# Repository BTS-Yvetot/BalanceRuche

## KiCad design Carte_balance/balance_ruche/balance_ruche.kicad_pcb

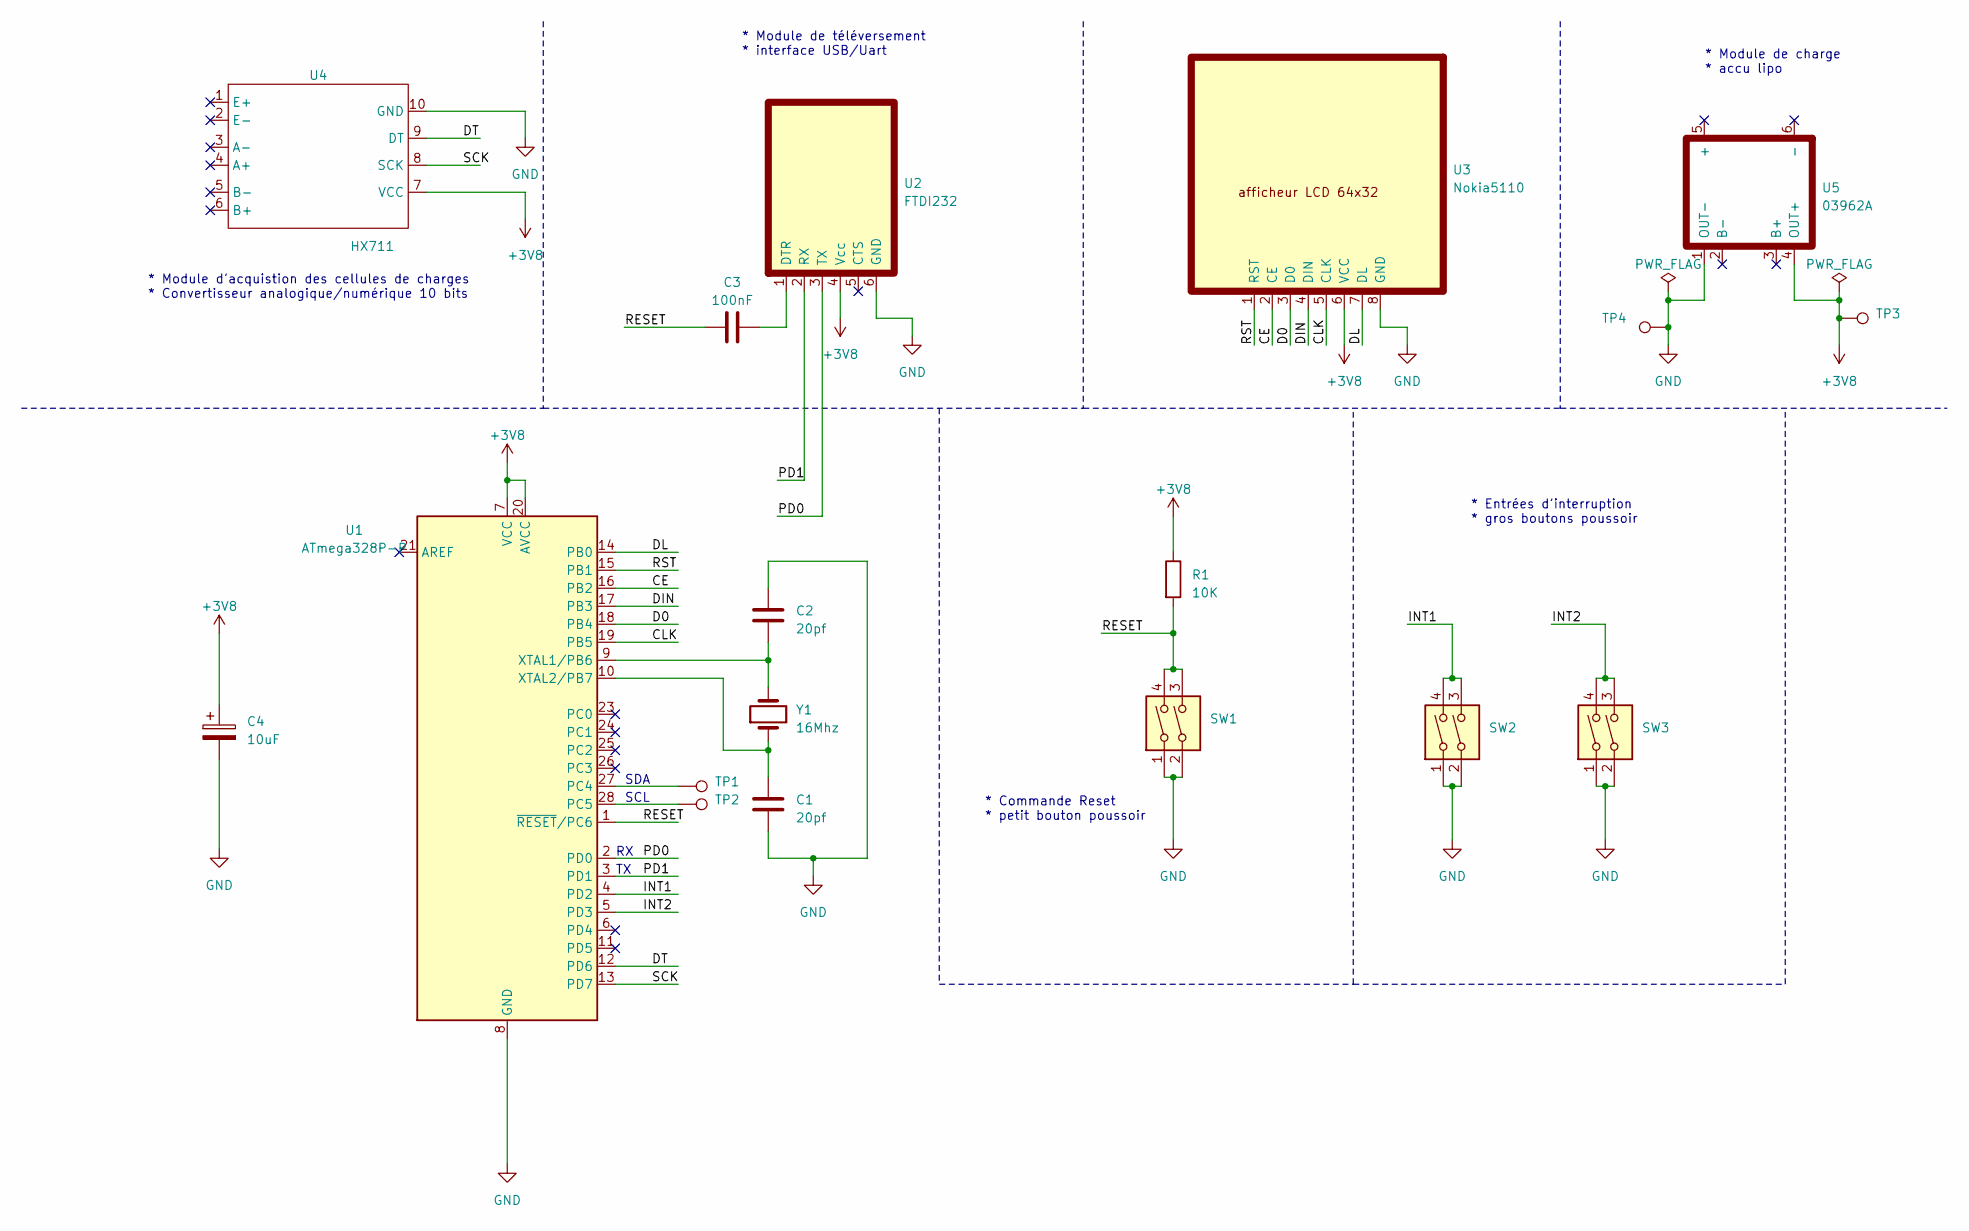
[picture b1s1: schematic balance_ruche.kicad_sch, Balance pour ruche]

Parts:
C1, C2: 20pf; C_Disc_D8.0mm_W5.0mm_P7.50mm
C3: 100nF; C_Rect_L7.2mm_W2.5mm_P5.00mm_FKS2_FKP2_MKS2_MKP2
C4: 10uF; CP_Radial_D5.0mm_P2.50mm
R1: 10K; R_Axial_DIN0309_L9.0mm_D3.2mm_P12.70mm_Horizontal
SW1: SW_DIP_x02; micro_switch
SW2, SW3: SW_DIP_x02; bouton_poussoir
TP1, TP2, TP3, TP4: TestPoint; TestPoint_THTPad_2.0x2.0mm_Drill1.0mm
U1: ATmega328P-P; DIP_28_Atmel328P
U2: FTDI232; FTDI232RL
U3: Nokia5110; Nokia5510
U4: HX711
U5: 03962A; Charger_accu
Y1: 16Mhz; Crystal_HC49-4H_Vertical

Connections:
+3V8: C4.1, R1.1, TP3.1, U1.7 (VCC), U1.20 (AVCC), U2.4 (Vcc), U3.6 (VCC), U4.7 (VCC), U5.4 (OUT+)
/CE: U1.16 (PB2), U3.2 (CE)
/CLK: U1.19 (PB5), U3.5 (CLK)
/D0: U1.18 (PB4), U3.3 (D0)
/DIN: U1.17 (PB3), U3.4 (DIN)
/DL: U1.14 (PB0), U3.7 (DL)
/DT: U1.12 (PD6), U4.9 (DT)
/INT1: SW2.3, SW2.4, U1.4 (PD2)
/INT2: SW3.3, SW3.4, U1.5 (PD3)
/PD0: U1.2 (PD0), U2.3 (TX)
/PD1: U1.3 (PD1), U2.2 (RX)
/RESET: C3.1, R1.2, SW1.3, SW1.4, U1.1 (~RESET/PC6)
/RST: U1.15 (PB1), U3.1 (RST)
/SCK: U1.13 (PD7), U4.8 (SCK)
GND: C1.2, C2.1, C4.2, SW1.1, SW1.2, SW2.1, SW2.2, SW3.1, SW3.2, TP4.1, U1.8 (GND), U1.22 (GND), U2.6 (GND), U3.8 (GND), U4.10 (GND), U5.1 (OUT-)
unnamed: TP1.1, U1.27 (PC4)
unnamed: TP2.1, U1.28 (PC5)
unnamed: C2.2, U1.9 (XTAL1/PB6), Y1.2
unnamed: C1.1, U1.10 (XTAL2/PB7), Y1.1
unnamed: C3.2, U2.1 (DTR)

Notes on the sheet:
* Commande Reset * petit bouton poussoir
* Module de charge * accu lipo
SDA
SCL
* Entrées d'interruption * gros boutons poussoir
* Module de téléversement * interface USB/Uart
* Module d'acquistion des cellules de charges * Convertisseur analogique/numérique 10 bits

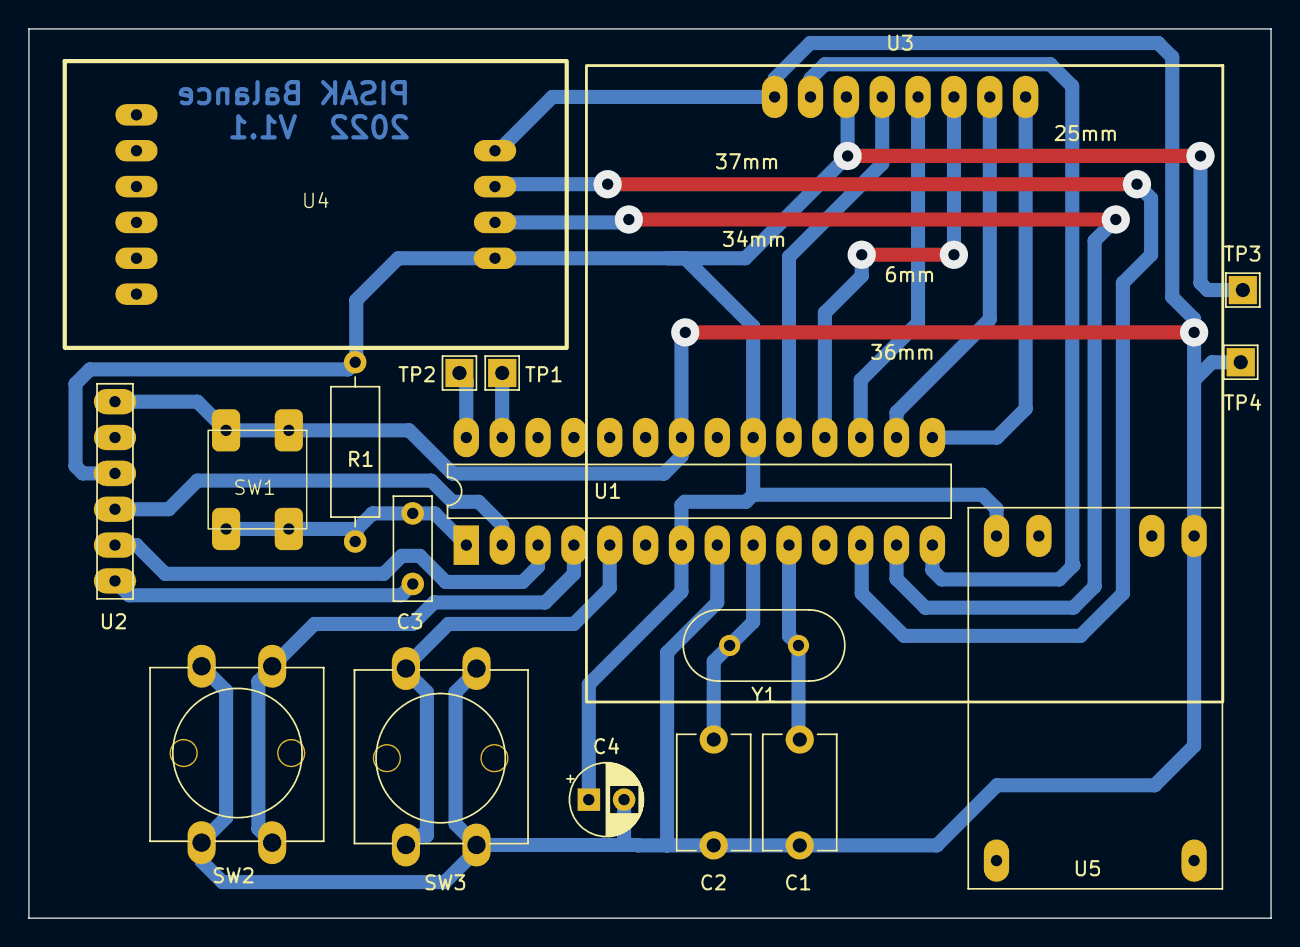
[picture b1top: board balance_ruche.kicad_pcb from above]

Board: 2 copper layers, 88.0 x 63.0 mm, 18 parts (0 on the bottom side), 20 nets.

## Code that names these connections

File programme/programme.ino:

#include <SPI.h>
#include <avr/wdt.h>
#include <avr/sleep.h>
#include "HX711.h"
#include "fonction.h"

#define RST 9  //broche PB1 patte 15 sur l'atmel reset de l'afficheur SPI
#define CE  10 //broche PB2 patte 16 sur l'atmel chip enable de l'afficheur SPI
#define DO  12 //broche PB4 patte 18 sur l'atmel miso de l'afficheur SPI
#define DL  8  //broche PB0 patte 14 sur l'atmel retro eclairage de l'afficheur
#define CLK 13 //broche PB5 patte 19 sur l'atmel
#define DIN 11 //broche PB3 patte 17 sur l'atmel

#define DT  6  //ligne data du convertisseur pour cellule de charge HX711 (broche PD6 patte 12 sur l'atmel)
#define SCK 7  //ligne d'horloge pour le convertisseur HX711 (broche PD7 patte 13 sur l'atmel)

#define debug false

//afficheur NOKIA 5510

#include <Adafruit_GFX.h>
#include <Adafruit_PCD8544.h>

//Branchement des deux signaux Dout et Clock sur PD6 et PD7
const int LOADCELL_DOUT_PIN = DT;    
const int LOADCELL_SCK_PIN = SCK;       


//on garde les broches 4 et 5 de l'atmel (PD2 et PD3) comme entree d'interuption pour les futurs boutons poussoirs
//d'ou le deplacement du reset de l'afficheur LCD

//instanciation du capteur et de l'afficheur
//afficheur nokia 5110 utilisé en SPI hardware donc broche 11 et 13
//nécessairement utilisées (patte 17 pour mosi et 19 pour clock sur l'atmel 328p)
Adafruit_PCD8544 lcd = Adafruit_PCD8544(CLK, DIN, DO, CE, RST);     //afficheur Nokia sur liaison SPI hardware
                                                      

//variable pour les routines d'interruption

volatile bool routineWDT = false;
volatile bool routineINT0 = false;
volatile bool routineINT1 = false;
volatile float poids=0.0;
volatile unsigned long chrono;
volatile unsigned int compteur=0;

//traitement des trois interruptions possible (watchdog,INT0 sur PD2 et INT1 sur PD3)
ISR(WDT_vect) {
  routineWDT = true;
  compteur++;
}

ISR(INT0_vect) {                             //mise en mémoire du poids sur PD2
  EIMSK = 0x00;                              //desactivation des inter externes
  WDTCSR = (1 << WDCE) | (1 << WDE);         //desactivation du chien de garde
  WDTCSR = 0b0000000;                        //
  routineINT0 = true;
}

ISR(INT1_vect) {                             //rétro-eclairage sur PD3
  EIMSK = 0x00;                              //desactivation des inter externes
  WDTCSR = (1 << WDCE) | (1 << WDE);         //desactivation du chien de garde
  WDTCSR = 0b0000000;                        //
  chrono=millis();
  routineINT1 = true;
}  


int main (void){
  init();                             //initialisation pour utiliser l'environnement arduino
  HX711 balance;                      //instanciation d'un objet HX711
  boolean start=true;                 //variable pour le premier lancement du programme
  float memPoids=0.0; 

#if debug
  Serial.begin(9600);
#endif

//broche retro eclairage et interuption
  pinMode(DL, OUTPUT);         //retro_eclairage actif a l'etat haut
  pinMode(2, INPUT_PULLUP);   //interupteur sur broche D2 INT0 : mise en memoire
  pinMode(3, INPUT_PULLUP);   //interupteur sur broche D3 INT1 : retro-eclairage
 
//initialisation de la balance  
  balance.begin(LOADCELL_DOUT_PIN, LOADCELL_SCK_PIN,128);   //gain de 128 sur le channel A du convertisseur (le 32 reservé pour le canal B)

//(tare + facteur de convertion)
  while (!balance.is_ready());                              //attention !! fonction bloquante tant que Dout n'est pas au niveau bas
  balance.set_scale(2297.f);                                //valeur trouvee après la procedure de calibration
  balance.tare(10);                                         //permet de soustraire la valeur au démarrage pour afficher 0 (tarage de la balance) avec 10 mesures

// Afficheur lcd
  lcd.begin();
  lcd.setRotation(0);         //(pose problème pour l'affichage de plusieur info sans clearDisplay !! laisser 0 par défaut)
  lcd.clearDisplay();
  lcd.setContrast(60);        //!!!! a régler pour chaque afficheur....
  lcd.display();

#if debug
  Serial.println("balance prête !!");
#endif

  //affichage de la page de présentation
  lcd.clearDisplay();
  lcd.cp437(true);                    // Utilisation des 256 caractères de la police Cp437
  lcd.drawRect(0, 0, 83, 47, BLACK);  // cadre de l'ecran
  lcd.setTextSize(1);                 // taille normale 1:1 pixel soit 5x7 pixels
  lcd.setTextColor(BLACK);            // couleur unique
  lcd.setCursor(2,2);                 // affichage de la trame de la page
  lcd.print("mem :");
  lcd.setCursor(65,2);
  lcd.print("kg");
  lcd.setCursor(60,29);
  lcd.print(F(" Kg"));
  lcd.display();


  
  while(1){
//toute les 8 secondes ou la premiere fois 
    if(routineWDT || start){              //réveil par le chien de garde watchdog         

      start=false;                        //pour afficher les valeurs uniquement au premier lancement sans attendre 8 seconde
      poids=(balance.get_units(10)/10);
      if (poids<=0.0){                    // permet de gérer le poids si négatif
        poids=0.0;
      }
//mesure du poids
#if debug
      Serial.println(F("le watchdog à déclenché !"));
      Serial.print(poids,1);           //affiche la valeur en Kg avec 1 chiffre derrière la virgule (on tient compte ici du 
      Serial.println(" kg");                                //facteur de convertion (contrairement a get_value()
#endif

//gestion du retro eclairage      
      if (compteur>=1){
         digitalWrite(DL,LOW);             //gestion du rétro-éclairage
         compteur=0;
      }     
//effacement des anciennes données
      effacePoids(lcd);

//affichage des données
      //poids LCD
      lcd.setTextSize(2);              // taille normale 1:1 pixel soit 5x7 pixels
      lcd.setTextColor(BLACK, WHITE);  // couleur unique
      lcd.setCursor(4, 29);
      if (poids>=100.00){
        lcd.print(poids,1);
      }
      else {
        lcd.print(poids);
      }
      lcd.display();
      balance.power_down();                                 //place le capteur en basse consommation
      routineWDT=false;           
    }
    //si appuye sur le bouton de droite 
    if (routineINT0) {
      wdt_reset();
      digitalWrite(DL,HIGH);                       //allumage du rétro-éclairage
      balance.power_down(); 
      routineINT0 = false;
      wdt_reset();
#if debug
      Serial.println("INT0 a declenche !!");
      Serial.println("fin de la routine INT0");
#endif
    }
    //si appuye sur le bouton de gauche
    if (routineINT1) {
      memPoids=poids;
      effaceMem(lcd);
      lcd.setTextSize(1);              // taille normale 1:1 pixel soit 5x7 pixels
      lcd.setCursor(35, 2);
      if(memPoids>=100.00){
        lcd.print(memPoids,1);
      }
      else{
        lcd.print(memPoids);
      }
      lcd.display();
      while((!digitalRead(3))&&((millis()-chrono)<3000));
      if(!digitalRead(3)){               //appuie sur le bouton de gauche pendant 3 secondes
        effacePoids(lcd);
        balance.tare(10);
        poids=(balance.get_units(10)/10);
        lcd.setTextSize(2);              // taille normale 1:1 pixel soit 5x7 pixels
        lcd.setTextColor(BLACK, WHITE);  // couleur unique
        lcd.setCursor(4, 29);
        if (poids<=0.0){
          poids=0.0;
        }
        lcd.print(poids);
        lcd.display();
        while(!digitalRead(3));         //tant que l'on a pas relaché le bouton
        wdt_reset();
      }
#if debug
      Serial.println("INT1 a declenche !!");
      Serial.println("fin de la routine INT1");
#endif
      balance.power_down();
      routineINT1 = false;            //interuption prise en compte
    }

    //autorise les interruptions des deux boutons poussoirs
    EIFR = 0b00000011; //efface les drapeaux avant de valider les interruptions à nouveau!!
    EIMSK = 0x03;     //validation des interruptions sur les pattes PD2 et PD3 (INT0 et INT1)
    EICRA = 0b00001010; //front descendant sur INT0 et INT1 (compatible avec le mode sleep utilisé)

    //autorise les interruptions du watchdog (toutes les 8 secondes )
    wdt_reset();
    WDTCSR = (1 << WDCE) | (1 << WDE);          // Déverrouille les bits de configuration du Watchdog (procédure spécifiée par le fabricant)
    WDTCSR = 0b01100001;                        // Mise à 1 des bits WDP3 et WDIE, pour activer les interruption toutes les 8 secondes
                  
    // mise en sommeil
    set_sleep_mode(SLEEP_MODE_PWR_DOWN);
    sleep_enable();
    // Et on met le µC en sommeil maintenant
#if debug
    Serial.println("Mise en sommeil du µC");
    Serial.println("");
    Serial.flush();         // On attend la fin de la transmission des données séries, avant de mettre le microcontrôleur en sommeil
#endif
    sleep_mode();
#if debug
    Serial.println("réveil!!");
#endif
    balance.power_up();                                   //active le capteur (sortie du mode basse consommation)
  }
  
}

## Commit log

2023-10-11 création du projet avec les fichiers existants
2023-11-22 Initiatisation du dépôt
